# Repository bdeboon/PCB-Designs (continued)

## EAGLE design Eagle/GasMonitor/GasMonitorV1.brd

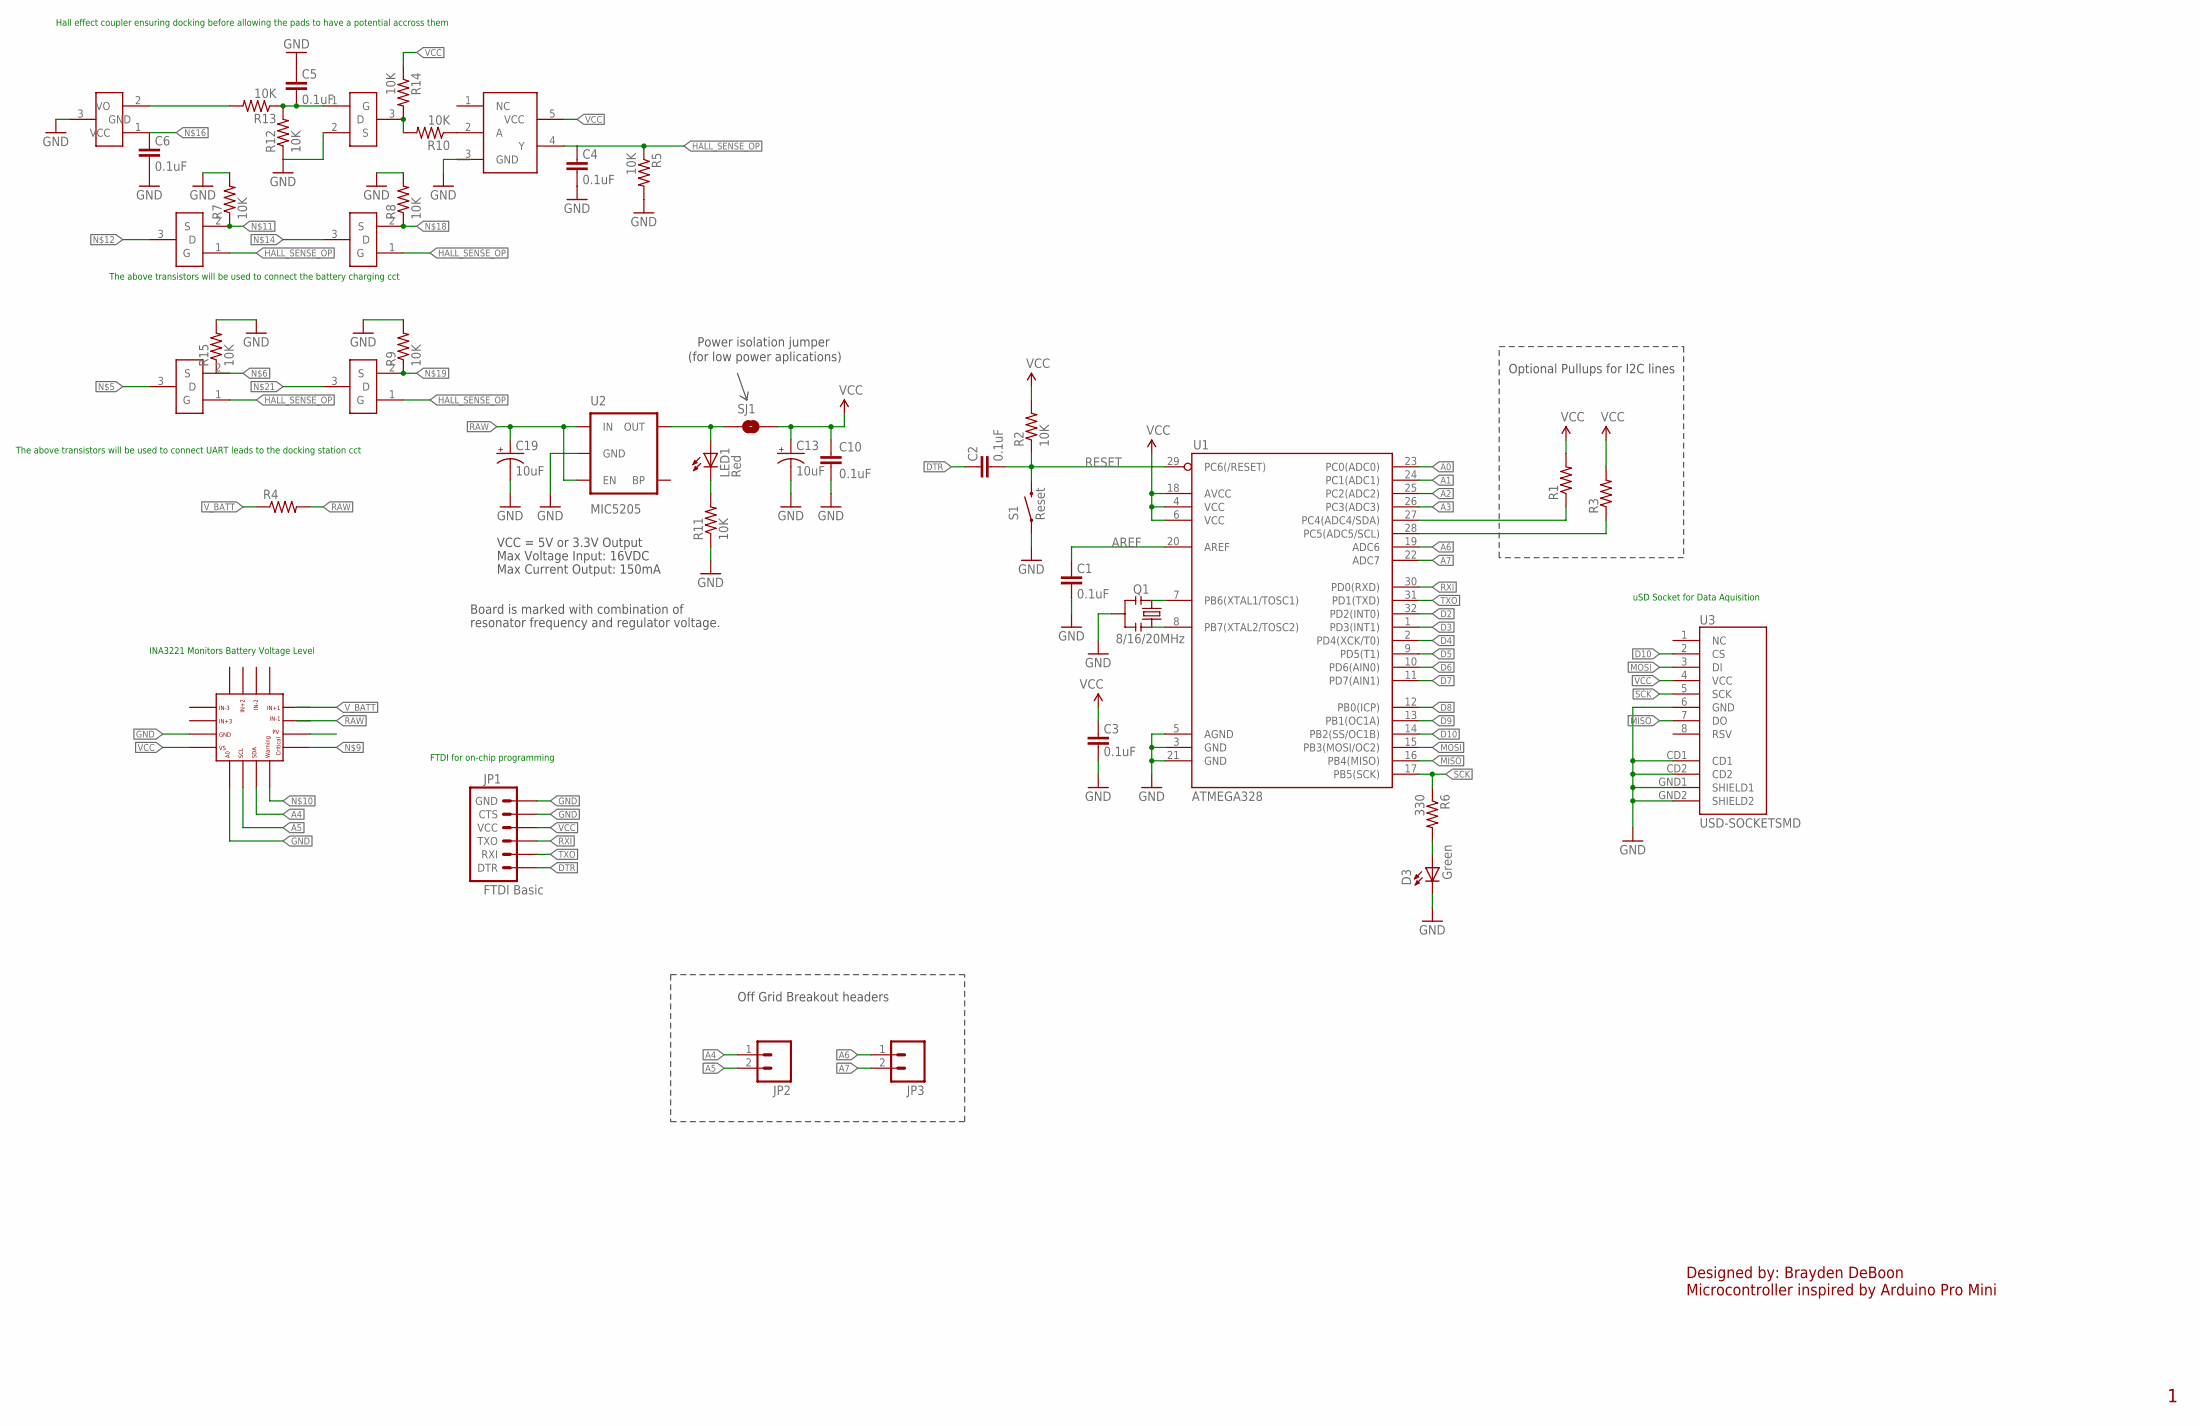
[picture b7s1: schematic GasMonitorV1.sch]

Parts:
C1, C2, C3, C4, C5, C6, C10: 0.1uF; 0603-CAP
C13, C19: 10uF; EIA3216
D3: Green; 0603-LED-ALT1
JP1: FTDI Basic; 1X06
JP2, JP3: M02PTH; 1X02
LED1: Red; 0603-LED-ALT1
Q1: 8/16/20MHz; RESONATOR-SMD-1:1
R1, R3: RESISTOR0603-RES; 0603-RES
R2, R5, R7, R8, R9, R10, R11, R12, R13, R14, R15: 10K; 0603-RES
R4: R-US_M1206; M1206
R6: 330; 0603-RES
S1: Reset; TACTILE-SWITCH-SMD-ALT01
SJ1: SOLDERJUMPERNC; SJ_2S
U1: ATMEGA328; TQFP32-08
U2: MIC5205; SOT23-5
U3: USD-SOCKETSMD; MICRO-SD-SOCKET-PP
U$1: INA3221; QFN16
U$2, U$3, U$4, U$5, U$6: MOSFET_SOT23; SOT-23
U$7: HALL_SENSE; SOT-23
U$8: INVERTER_SOT23-5; SOT-23-5

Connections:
A0: U1.23 (PC0(ADC0))
A1: U1.24 (PC1(ADC1))
A2: U1.25 (PC2(ADC2))
A3: U1.26 (PC3(ADC3))
A4: JP2.1, R1.1, U1.27 (PC4(ADC4/SDA)), U$1.7 (SDA)
A5: JP2.2, R3.1, U1.28 (PC5(ADC5/SCL)), U$1.6 (SCL)
A6: JP3.1, U1.19 (ADC6)
A7: JP3.2, U1.22 (ADC7)
AREF: C1.2, U1.20 (AREF)
D2: U1.32 (PD2(INT0))
D3: U1.1 (PD3(INT1))
D4: U1.2 (PD4(XCK/T0))
D5: U1.9 (PD5(T1))
D6: U1.10 (PD6(AIN0))
D7: U1.11 (PD7(AIN1))
D8: U1.12 (PB0(ICP))
D9: U1.13 (PB1(OC1A))
D10: U1.14 (PB2(SS/OC1B)), U3.2 (CS)
DTR: C2.2, JP1.1 (DTR)
GND: C1.1, C3.1, C4.1, C5.2, C6.1, C10.2, C13.C (-), C19.C (-), D3.C, JP1.5 (CTS), JP1.6 (GND), Q1.2, R5.2, R7.2, R8.2, R9.2, R11.1, R12.1, R15.2, S1.1, S1.2 (1), U1.3 (GND), U1.5 (AGND), U1.21 (GND), U2.2 (GND), U3.6 (GND), U3.CD1, U3.CD2, U3.GND1 (SHIELD1), U3.GND2 (SHIELD2), U$1.3 (GND), U$1.5 (A0), U$6.2 (S), U$7.3 (GND), U$8.3 (GND)
HALL_SENSE_OP: C4.2, R5.1, U$2.1 (G), U$3.1 (G), U$4.1 (G), U$5.1 (G), U$8.4 (Y)
MISO: U1.16 (PB4(MISO)), U3.7 (DO)
MOSI: U1.15 (PB3(MOSI/OC2)), U3.3 (DI)
unnamed: Q1.3, U1.8 (PB7(XTAL2/TOSC2))
unnamed: Q1.1, U1.7 (PB6(XTAL1/TOSC1))
unnamed: LED1.A, SJ1.1, U2.5 (OUT)
unnamed: LED1.C, R11.2
unnamed: D3.A, R6.2
unnamed: R7.1, U$2.2 (S)
unnamed: C5.1, R12.2, R13.1, U$6.1 (G)
unnamed: R13.2, U$7.2 (VO)
unnamed: C6.2, U$7.1 (VCC)
unnamed: R10.2, R14.2, U$6.3 (D)
unnamed: R8.1, U$3.2 (S)
unnamed: R9.1, U$5.2 (S)
unnamed: R10.1, U$8.2 (A)
RAW: C19.A (+), R4.2, U2.1 (IN), U2.3 (EN)
RESET: C2.1, R2.1, S1.3 (2), S1.4 (2), U1.29 (PC6(/RESET))
RXI: JP1.3 (TXO), U1.30 (PD0(RXD))
SCK: R6.1, U1.17 (PB5(SCK)), U3.5 (SCK)
TXO: JP1.2 (RXI), U1.31 (PD1(TXD))
VCC: C3.2, C10.1, C13.A (+), JP1.4 (VCC), R1.2, R2.2, R3.2, R14.1, SJ1.2, U1.4 (VCC), U1.6 (VCC), U1.18 (AVCC), U3.4 (VCC), U$1.4 (VS), U$8.5 (VCC)
V_BATT: R4.1

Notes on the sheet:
Max Voltage Input: 16VDC
Max Current Output: 150mA
Board is marked with combination of
resonator frequency and regulator voltage.
VCC = 5V or 3.3V Output
Optional Pullups for I2C lines
Off Grid Breakout headers
Power isolation jumper
(for low power aplications)
Designed by: Brayden DeBoon Microcontroller inspired by Arduino Pro Mini
The above transistors will be used to connect the battery charging cct
The above transistors will be used to connect UART leads to the docking station cct
Hall effect coupler ensuring docking before allowing the pads to have a potential accross them
INA3221 Monitors Battery Voltage Level
FTDI for on-chip programming
uSD Socket for Data Aquisition

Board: 2 copper layers, 43 parts (0 on the bottom side), 30 nets, no tracks yet.

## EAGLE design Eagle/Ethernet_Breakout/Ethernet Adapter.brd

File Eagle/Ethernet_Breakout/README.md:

# Ethernet Breakout

This board is intended to utilize the cost and convenience of CAT5 and CAT6 cable standards, as well as maintain cable management in experimental setups. The board is very simple, just an ethernet receptacle that breaks out into eight individual terminal blocks.

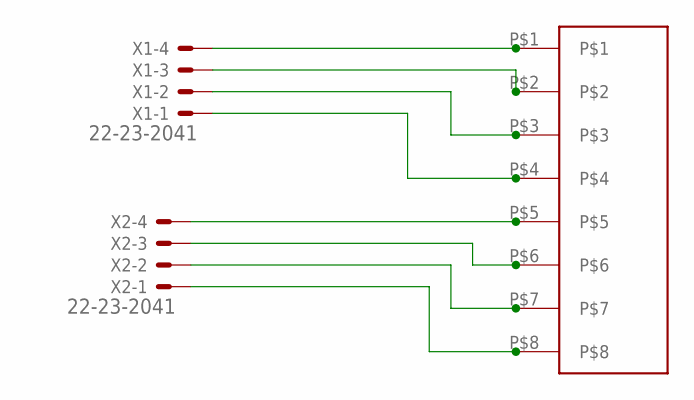
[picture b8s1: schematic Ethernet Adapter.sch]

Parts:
U$1: ETHERNETPORT
X1, X2: 22-23-2041

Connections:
unnamed: U$1.P$1, X1.4
unnamed: U$1.P$2, X1.3
unnamed: U$1.P$3, X1.2
unnamed: U$1.P$4, X1.1
unnamed: U$1.P$5, X2.4
unnamed: U$1.P$6, X2.3
unnamed: U$1.P$7, X2.2
unnamed: U$1.P$8, X2.1

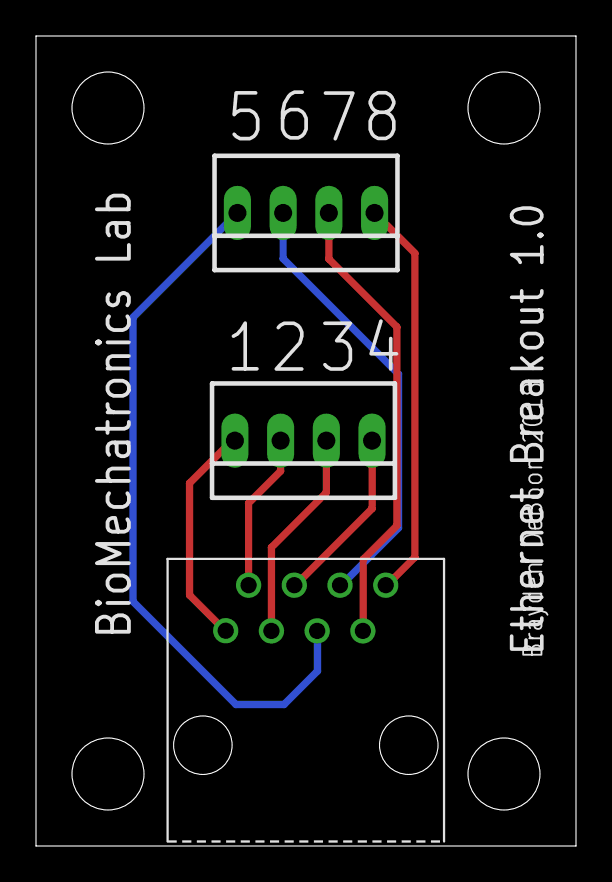
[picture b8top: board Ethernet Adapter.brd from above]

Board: 2 copper layers, 30.0 x 45.0 mm, 3 parts (0 on the bottom side), 8 nets.

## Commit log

2018-11-06 Added Killswitch Eagle Files and CAM
2018-11-09 Added CAM files
2018-11-16 Rename BusinessCard.md to README.md
2018-11-16 Added Motor Controller Board
2018-11-17 Added Gas Monitor Sch
2018-11-17 Rename Eagle/GasMonitorV1.sch to Eagle/GasMonitor/GasMonitorV1.sch
2019-01-17 Create DAQ Extension
2019-02-10 Added CAM files for LOC MAP
